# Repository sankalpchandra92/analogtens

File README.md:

# Analog TENS Circuit
This project is based on a TENS (Transcutaneous Electrical Nerve Stimulation) unit, which is used to temporarily treat chronic or acute pain by delivering low-voltage electrical currents to the affected area through the skin.
## Waveform Generation
- An astable 555 timer circuit was first designed to generate a pulse train with the desired frequency.

- The timing resistors were adjusted for the desired frequency.

- This signal was used to trigger a monostable 555 timer, configured to produce a pulse of the desired width on each falling edge.
- A differentiator circuit was then used to extract the falling edge of the monostable output, which was used to trigger a second monostable timer, producing an equal-width pulse.

- The timing resistors of the monostable stage circuit were adjusted for the desired pulse width.

- Final waveform was produced with a pulse width of about 200 &micro;s at a frequency of 14 Hz.
## Signal Conditioning
- The output signal from the first monostable timer is fed into a non-inverting operational amplifier to buffer and isolate the waveform.
- The signal from the second monostable timer is passed through an inverting operational amplifier to produce a polarity-reversed pulse.
- Both amplifier outputs are routed through current-limiting resistors to ensure safe delivery of the stimulation pulses.

- The circuit was simulated in LTspice with various output loads between 1 k&Omega; and 10 k&Omega; (representing typical skin resistance), verifying that the maximum output current remained below 3.5 mA.
## PCB Layout
The schematic was converted into a dual-layer PCB layout, designed for reliable hardware testing and future prototyping.

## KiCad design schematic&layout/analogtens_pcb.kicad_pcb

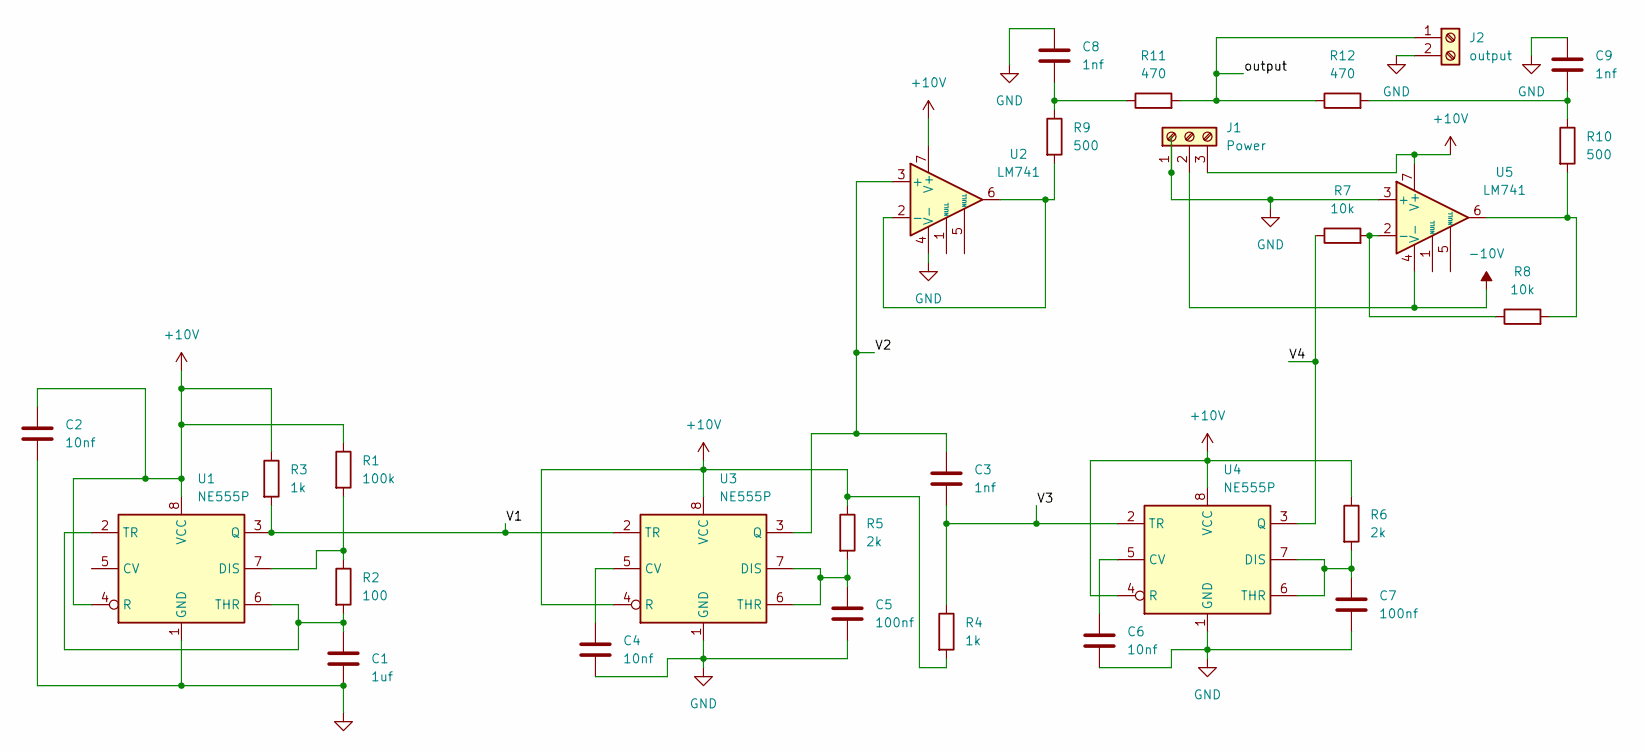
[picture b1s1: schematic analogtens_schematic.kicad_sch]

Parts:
C1: 1uf; C_Disc_D4.3mm_W1.9mm_P5.00mm
C2, C4, C6: 10nf; C_Axial_L5.1mm_D3.1mm_P10.00mm_Horizontal
C3, C8, C9: 1nf; C_Disc_D4.3mm_W1.9mm_P5.00mm
C5, C7: 100nf; C_Axial_L5.1mm_D3.1mm_P10.00mm_Horizontal
J1: Power; TerminalBlock_Altech_AK300-3_P5.00mm
J2: output; TestPoint_2Pads_Pitch2.54mm_Drill0.8mm
R1: 100k; R_Axial_DIN0207_L6.3mm_D2.5mm_P10.16mm_Horizontal
R2: 100; R_Axial_DIN0207_L6.3mm_D2.5mm_P10.16mm_Horizontal
R3, R4: 1k; R_Axial_DIN0207_L6.3mm_D2.5mm_P10.16mm_Horizontal
R5, R6: 2k; R_Axial_DIN0207_L6.3mm_D2.5mm_P10.16mm_Horizontal
R7, R8: 10k; R_Axial_DIN0207_L6.3mm_D2.5mm_P10.16mm_Horizontal
R9, R10: 500; R_Axial_DIN0207_L6.3mm_D2.5mm_P10.16mm_Horizontal
R11, R12: 470; R_Axial_DIN0207_L6.3mm_D2.5mm_P10.16mm_Horizontal
U1, U3, U4: NE555P; DIP-8_W7.62mm
U2, U5: LM741; DIP-8_W7.62mm

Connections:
+10V: C2.1, J1.3, R1.1, R3.1, R4.2, R5.1, R6.1, U1.4 (R), U1.8 (VCC), U2.7 (V+), U3.4 (R), U3.8 (VCC), U4.4 (R), U4.8 (VCC), U5.7 (V+)
-10V: J1.2, U5.4 (V-)
/V1: R3.2, U1.3 (Q), U3.2 (TR)
/V2: C3.1, U2.3 (+), U3.3 (Q)
/V3: C3.2, R4.1, U4.2 (TR)
/V4: R7.1, U4.3 (Q)
/output: J2.1, R11.2, R12.1
GND: C1.2, C2.2, C4.2, C5.2, C6.2, C7.2, C8.1, C9.1, J1.1, J2.2, U1.1 (GND), U2.4 (V-), U3.1 (GND), U4.1 (GND), U5.3 (+)
unnamed: C8.2, R9.1, R11.1
unnamed: C9.2, R10.1, R12.2
unnamed: R8.2, R10.2, U5.6
unnamed: R1.2, R2.1, U1.7 (DIS)
unnamed: C1.1, R2.2, U1.2 (TR), U1.6 (THR)
unnamed: R9.2, U2.2 (-), U2.6
unnamed: C4.1, U3.5 (CV)
unnamed: C5.1, R5.2, U3.6 (THR), U3.7 (DIS)
unnamed: C6.1, U4.5 (CV)
unnamed: C7.1, R6.2, U4.6 (THR), U4.7 (DIS)
unnamed: R7.2, R8.1, U5.2 (-)

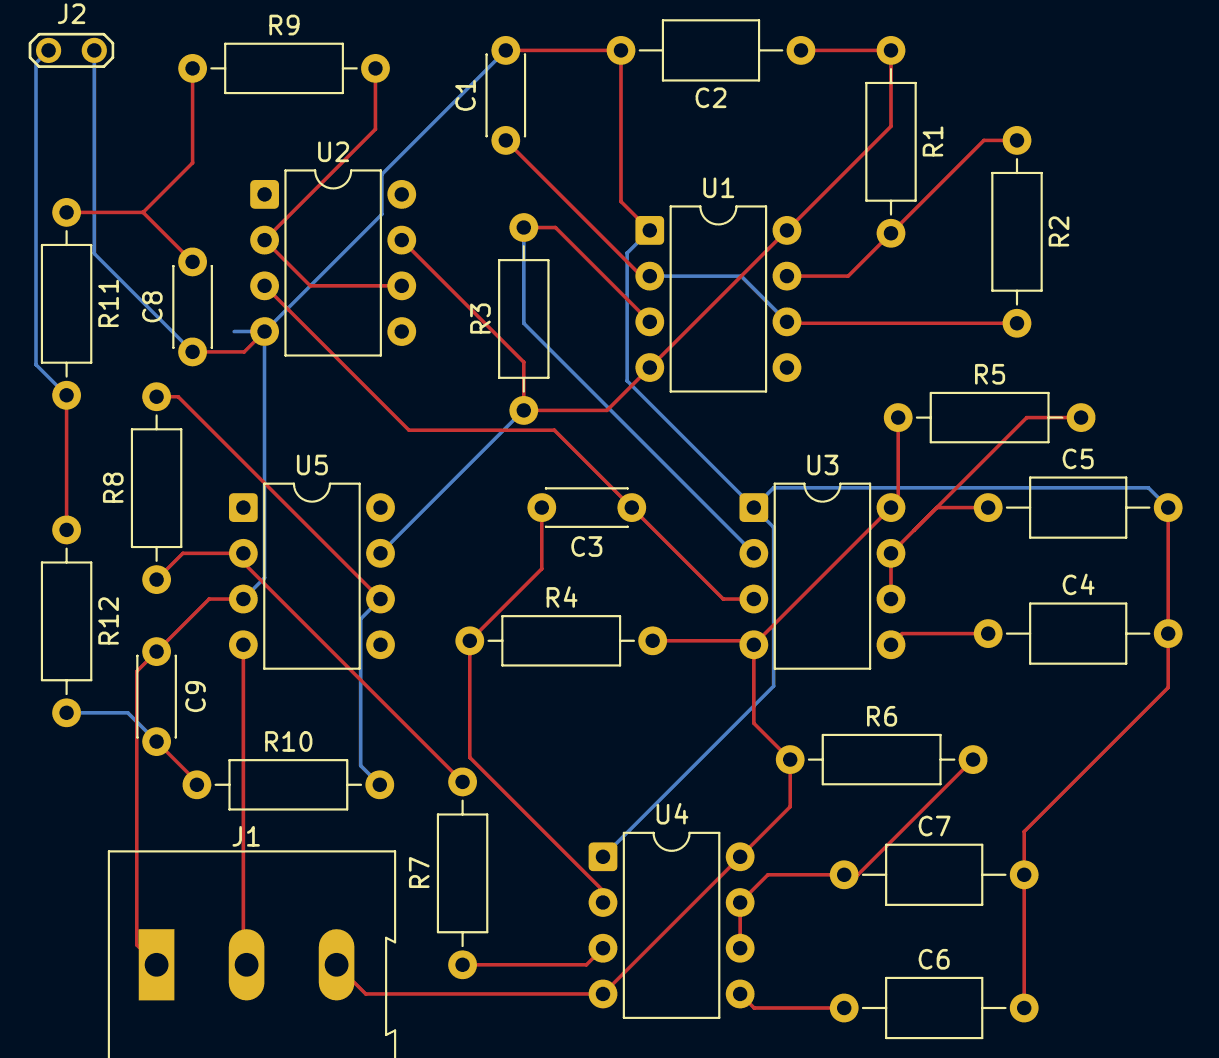
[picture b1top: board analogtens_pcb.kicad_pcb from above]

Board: 2 copper layers, 28 parts (0 on the bottom side), 19 nets.
